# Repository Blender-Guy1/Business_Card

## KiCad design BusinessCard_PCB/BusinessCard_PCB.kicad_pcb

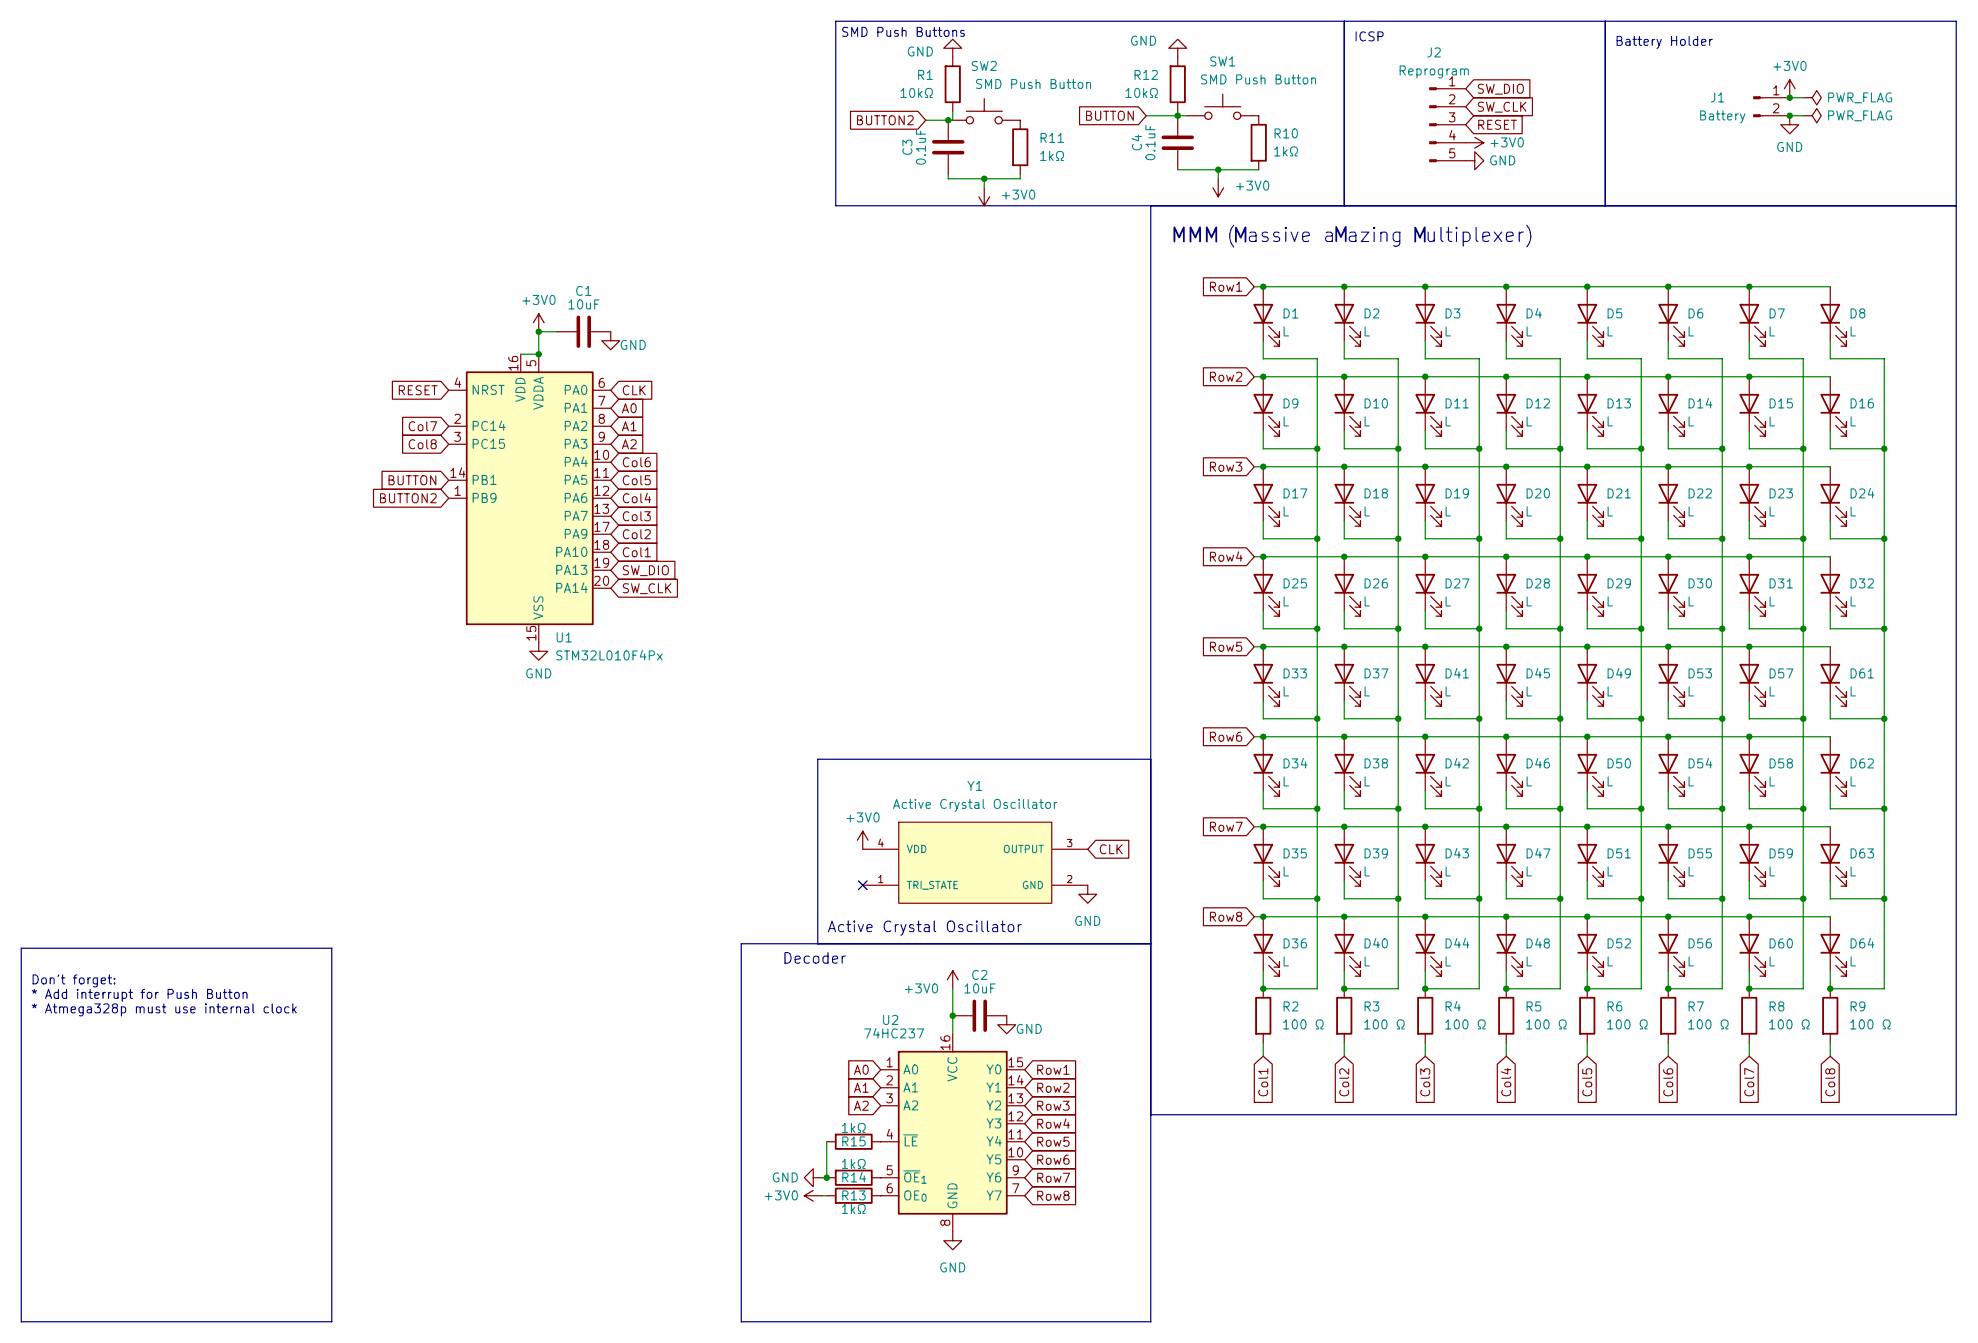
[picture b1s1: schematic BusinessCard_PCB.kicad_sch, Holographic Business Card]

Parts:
C1, C2: 10uF; C_0603_1608Metric; LCSC C70225
C3, C4: 0.1uF; C_0603_1608Metric; LCSC C1590
D1, D2, D3, D4, D5, D6, D7, D8, D9, D10, D11, D12, D13, D14, D15, D16, D17, D18, D19, D20, D21, D22, D23, D24, D25, D26, D27, D28, D29, D30, D31, D32, D33, D34, D35, D36, D37, D38, D39, D40, D41, D42, D43, D44, D45, D46, D47, D48, D49, D50, D51, D52, D53, D54, D55, D56, D57, D58, D59, D60, D61, D62, D63, D64: L; LED_0805_2012Metric; LCSC C434431
J1: Battery; CR2025 Circuit Board Battery Holder
J2: Reprogram; PinHeader_1x05_P2.54mm_Vertical
R1, R12: 10kΩ; R_0603_1608Metric; LCSC C15401
R2, R3, R4, R5, R6, R7, R8, R9: 100 Ω; R_0603_1608Metric; LCSC C3017758
R10, R11, R13, R14, R15: 1kΩ; R_0603_1608Metric; LCSC C14676
SW1, SW2: SMD Push Button; SW_SPST_TL3342; LCSC C2874421
U1: STM32L010F4Px; TSSOP-20_4.4x6.5mm_P0.65mm; LCSC C529415
U2: 74HC237; SOT-23-16 Thin
Y1: Active Crystal Oscillator; OSC_ECS-2520S25-250-FN-TR; PARTREV 2017; LCSC C1857764

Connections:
+3V0: C1.1, C2.1, C3.1, C4.1, J1.1, J2.4, R10.2, R11.2, R13.2, U1.5 (VDDA), U1.16 (VDD), U2.16 (VCC), Y1.4 (VDD)
A0: U1.7 (PA1), U2.1 (A0)
A1: U1.8 (PA2), U2.2 (A1)
A2: U1.9 (PA3), U2.3 (A2)
BUTTON: C4.2, R12.1, SW1.1, U1.14 (PB1)
BUTTON2: C3.2, R1.1, SW2.1, U1.1 (PB9)
CLK: U1.6 (PA0), Y1.3 (OUTPUT)
Col1: R2.2, U1.18 (PA10)
Col2: R3.2, U1.17 (PA9)
Col3: R4.2, U1.13 (PA7)
Col4: R5.2, U1.12 (PA6)
Col5: R6.2, U1.11 (PA5)
Col6: R7.2, U1.10 (PA4)
Col7: R8.2, U1.2 (PC14)
Col8: R9.2, U1.3 (PC15)
GND: C1.2, C2.2, J1.2, J2.5, R1.2, R12.2, R14.2, R15.2, U1.15 (VSS), U2.8 (GND), Y1.2 (GND)
unnamed: D1.1 (K), D9.1 (K), D17.1 (K), D25.1 (K), D33.1 (K), D34.1 (K), D35.1 (K), D36.1 (K), R2.1
unnamed: D2.1 (K), D10.1 (K), D18.1 (K), D26.1 (K), D37.1 (K), D38.1 (K), D39.1 (K), D40.1 (K), R3.1
unnamed: D3.1 (K), D11.1 (K), D19.1 (K), D27.1 (K), D41.1 (K), D42.1 (K), D43.1 (K), D44.1 (K), R4.1
unnamed: D4.1 (K), D12.1 (K), D20.1 (K), D28.1 (K), D45.1 (K), D46.1 (K), D47.1 (K), D48.1 (K), R5.1
unnamed: D5.1 (K), D13.1 (K), D21.1 (K), D29.1 (K), D49.1 (K), D50.1 (K), D51.1 (K), D52.1 (K), R6.1
unnamed: D6.1 (K), D14.1 (K), D22.1 (K), D30.1 (K), D53.1 (K), D54.1 (K), D55.1 (K), D56.1 (K), R7.1
unnamed: D7.1 (K), D15.1 (K), D23.1 (K), D31.1 (K), D57.1 (K), D58.1 (K), D59.1 (K), D60.1 (K), R8.1
unnamed: D8.1 (K), D16.1 (K), D24.1 (K), D32.1 (K), D61.1 (K), D62.1 (K), D63.1 (K), D64.1 (K), R9.1
unnamed: R10.1, SW1.2
unnamed: R11.1, SW2.2
unnamed: R13.1, U2.6 (OE_{0})
unnamed: R15.1, U2.4 (~LE)
unnamed: R14.1, U2.5 (~OE_{1})
RESET: J2.3, U1.4 (NRST)
Row1: D1.2 (A), D2.2 (A), D3.2 (A), D4.2 (A), D5.2 (A), D6.2 (A), D7.2 (A), D8.2 (A), U2.15 (Y0)
Row2: D9.2 (A), D10.2 (A), D11.2 (A), D12.2 (A), D13.2 (A), D14.2 (A), D15.2 (A), D16.2 (A), U2.14 (Y1)
Row3: D17.2 (A), D18.2 (A), D19.2 (A), D20.2 (A), D21.2 (A), D22.2 (A), D23.2 (A), D24.2 (A), U2.13 (Y2)
Row4: D25.2 (A), D26.2 (A), D27.2 (A), D28.2 (A), D29.2 (A), D30.2 (A), D31.2 (A), D32.2 (A), U2.12 (Y3)
Row5: D33.2 (A), D37.2 (A), D41.2 (A), D45.2 (A), D49.2 (A), D53.2 (A), D57.2 (A), D61.2 (A), U2.11 (Y4)
Row6: D34.2 (A), D38.2 (A), D42.2 (A), D46.2 (A), D50.2 (A), D54.2 (A), D58.2 (A), D62.2 (A), U2.10 (Y5)
Row7: D35.2 (A), D39.2 (A), D43.2 (A), D47.2 (A), D51.2 (A), D55.2 (A), D59.2 (A), D63.2 (A), U2.9 (Y6)
Row8: D36.2 (A), D40.2 (A), D44.2 (A), D48.2 (A), D52.2 (A), D56.2 (A), D60.2 (A), D64.2 (A), U2.7 (Y7)
SW_CLK: J2.2, U1.20 (PA14)
SW_DIO: J2.1, U1.19 (PA13)

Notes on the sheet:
Active Crystal Oscillator
Battery Holder
Don't forget: * Add interrupt for Push Button * Atmega328p must use internal clock
( assive a azing ultiplexer)
ICSP
SMD Push Buttons
Decoder
MMM

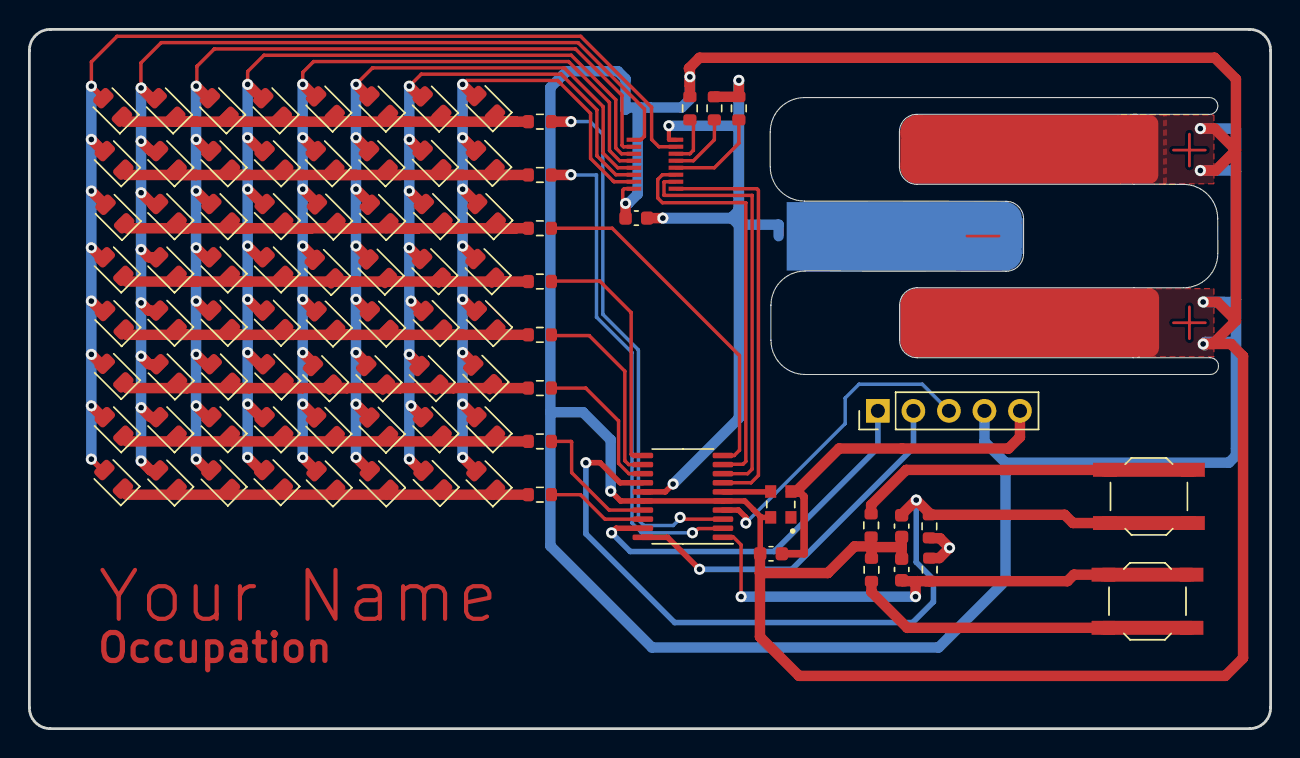
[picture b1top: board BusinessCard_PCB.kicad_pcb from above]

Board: 2 copper layers, 88.8 x 50.0 mm, 90 parts (0 on the bottom side), 40 nets.

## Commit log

2025-08-08 Added KiCAD File
    I added the KiCAD Files to the Repository.
2025-08-13 idk changes
2025-08-13 added battery holder
